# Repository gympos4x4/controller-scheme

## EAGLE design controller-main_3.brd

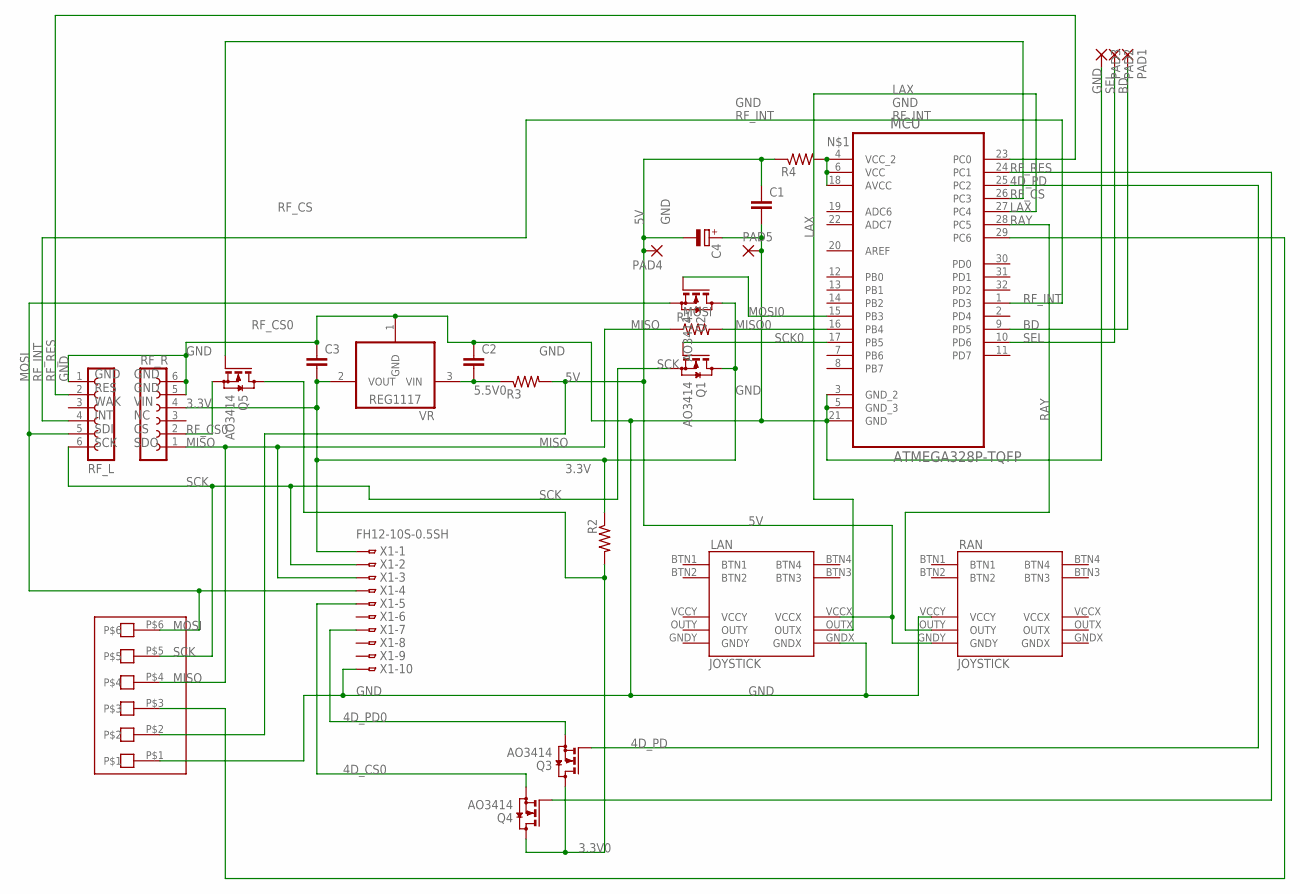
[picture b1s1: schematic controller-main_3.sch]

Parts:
C1, C2, C3: C-EUC1206; C1206
C4: CPOL-EU153CLV-0505; 153CLV-0505
LAN: JOYSTICK
MCU: ATMEGA328P-TQFP; QFP80P900X900X120-32N
PAD1, PAD2, PAD3: SMD2; SMD1,27-2,54
PAD4, PAD5: SMD5; SMD2,54-5,08
Q1, Q2, Q3, Q4, Q5: AO3414; SOT23
R1, R2, R3, R4: R-US_R1206; R1206
RAN: JOYSTICK
RF_L: FE06-1; FE06
RF_R: FE06-1; FE06
U$1: JTECH-6PV; PAK-6PV
VR: REG1117; SOT223
X1: FH12-10S-0.5SH

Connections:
3.3V: C3.2, Q1.3 (D), Q2.3 (D), R2.1, RF_R.4, VR.2 (VOUT), X1.1
3.3V0: Q3.3 (D), Q4.3 (D), Q5.3 (D), R2.2
4D_CS: MCU.24 (PC1), Q4.1 (G)
4D_CS0: Q4.2 (S), X1.5
4D_PD: MCU.25 (PC2), Q3.1 (G)
4D_PD0: Q3.2 (S), X1.7
5.5V0: C2.2, R3.1, VR.3 (VIN)
5V: C1.1, C4.-, LAN.VCCX, PAD4.1, R3.2, R4.1, RAN.GNDY, U$1.P$2
BD: MCU.9 (PD5), PAD1.1
GND: C1.2, C2.1, C3.1, C4.+, LAN.GNDX, MCU.3 (GND_2), MCU.5 (GND_3), MCU.21 (GND), PAD3.1, PAD5.1, RAN.VCCY, RF_L.1, RF_R.5, RF_R.6, U$1.P$1, VR.1 (GND), X1.10
LAX: LAN.OUTX, MCU.27 (PC4)
MISO: R1.1, RF_R.1, U$1.P$4, X1.3
MISO0: MCU.16 (PB4), R1.2
MOSI: Q2.2 (S), RF_L.5, U$1.P$6, X1.4
MOSI0: MCU.15 (PB3), Q2.1 (G)
unnamed: MCU.4 (VCC_2), MCU.6 (VCC), MCU.18 (AVCC), R4.2
RAY: MCU.28 (PC5), RAN.OUTY
RF_CS: MCU.26 (PC3), Q5.1 (G)
RF_CS0: Q5.2 (S), RF_R.2
RF_INT: MCU.1 (PD3), RF_L.4
RF_RES: MCU.23 (PC0), RF_L.2
RST: MCU.29 (PC6), U$1.P$3
SCK: Q1.2 (S), RF_L.6, U$1.P$5, X1.2
SCK0: MCU.17 (PB5), Q1.1 (G)
SEL: MCU.10 (PD6), PAD2.1

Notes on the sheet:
GND RES WAK INT SDI SCK
GND GND VIN NC CS SDO

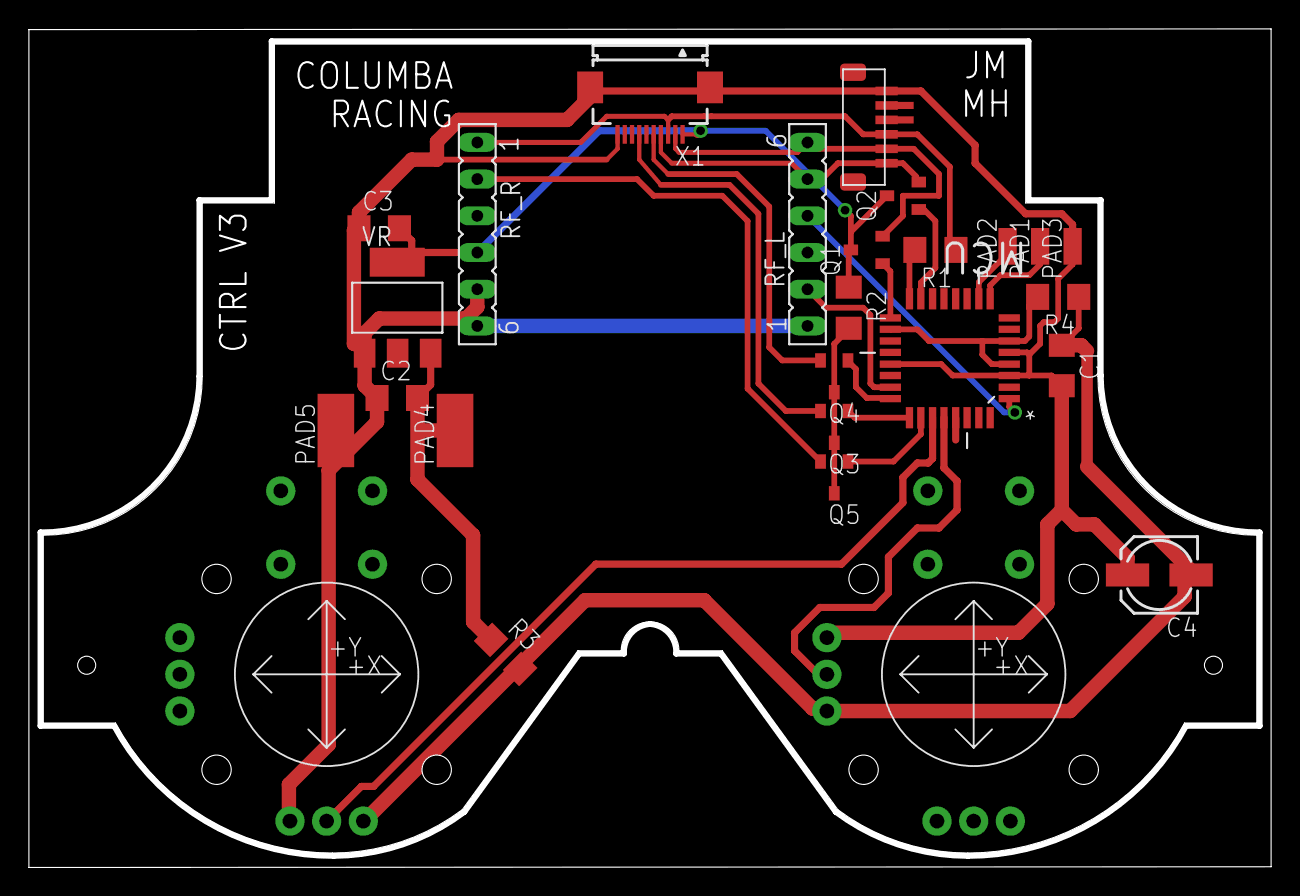
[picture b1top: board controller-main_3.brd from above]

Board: 2 copper layers, 85.6 x 57.6 mm, 26 parts (0 on the bottom side), 25 nets.

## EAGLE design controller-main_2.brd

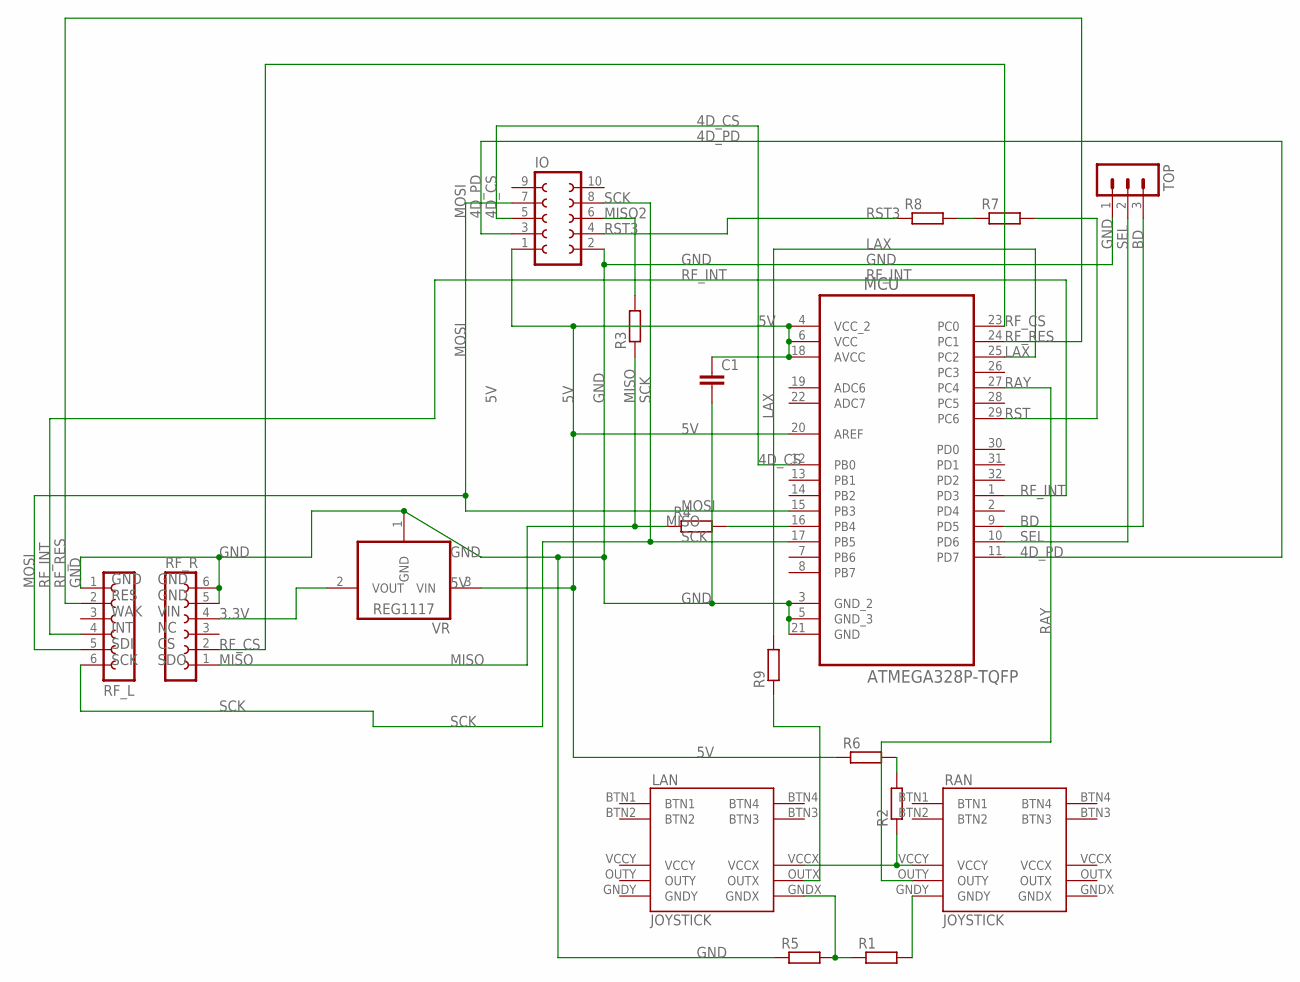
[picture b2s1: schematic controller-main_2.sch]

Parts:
C1: C-EUC1206; C1206
IO: FE05-2W
LAN: JOYSTICK
MCU: ATMEGA328P-TQFP; QFP80P900X900X120-32N
R1, R2, R3, R4, R5, R6, R7, R8, R9: R-EU_M1206; M1206
RAN: JOYSTICK
RF_L: FE06-1; FE06
RF_R: FE06-1; FE06
TOP: MA03-1
VR: REG1117; SOT223

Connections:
3.3V: RF_R.4, VR.2 (VOUT)
4D_CS: IO.5, MCU.12 (PB0)
4D_PD: IO.3, MCU.11 (PD7)
5V: C1.1, IO.1, MCU.4 (VCC_2), MCU.6 (VCC), MCU.18 (AVCC), MCU.20 (AREF), R6.1, VR.3 (VIN)
5V2: R2.2, R6.2
5V_R: LAN.VCCX, R2.1, RAN.VCCY
BD: MCU.9 (PD5), TOP.3
GND: C1.2, IO.2, MCU.3 (GND_2), MCU.5 (GND_3), MCU.21 (GND), R5.1, RF_L.1, RF_R.5, RF_R.6, TOP.1, VR.1 (GND)
GND2: LAN.GNDX, R1.1, R5.2
LAX: MCU.25 (PC2), R9.2
LAX2: LAN.OUTX, R9.1
MISO: R3.1, R4.1, RF_R.1
MISO2: IO.6, R3.2
MISO3: MCU.16 (PB4), R4.2
MOSI: IO.7, MCU.15 (PB3), RF_L.5
unnamed: R1.2, RAN.GNDY
RAY: MCU.27 (PC4), RAN.OUTY
RF_CS: MCU.23 (PC0), RF_R.2
RF_INT: MCU.1 (PD3), RF_L.4
RF_RES: MCU.24 (PC1), RF_L.2
RST: MCU.29 (PC6), R7.2
RST2: R7.1, R8.2
RST3: IO.4, R8.1
SCK: IO.8, MCU.17 (PB5), RF_L.6
SEL: MCU.10 (PD6), TOP.2

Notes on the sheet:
GND RES WAK INT SDI SCK
GND GND VIN NC CS SDO

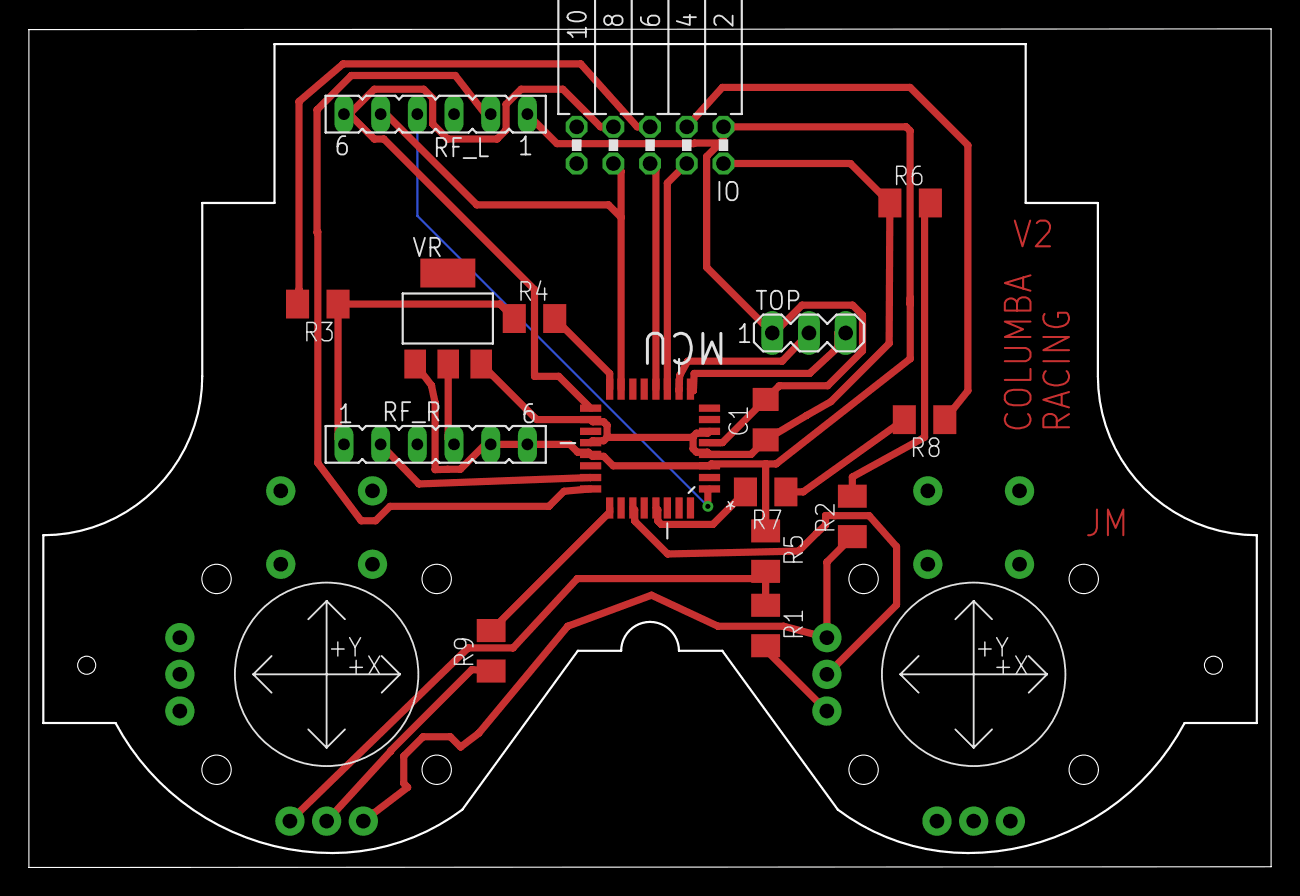
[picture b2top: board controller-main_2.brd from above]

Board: 2 copper layers, 85.8 x 57.9 mm, 18 parts (0 on the bottom side), 25 nets.

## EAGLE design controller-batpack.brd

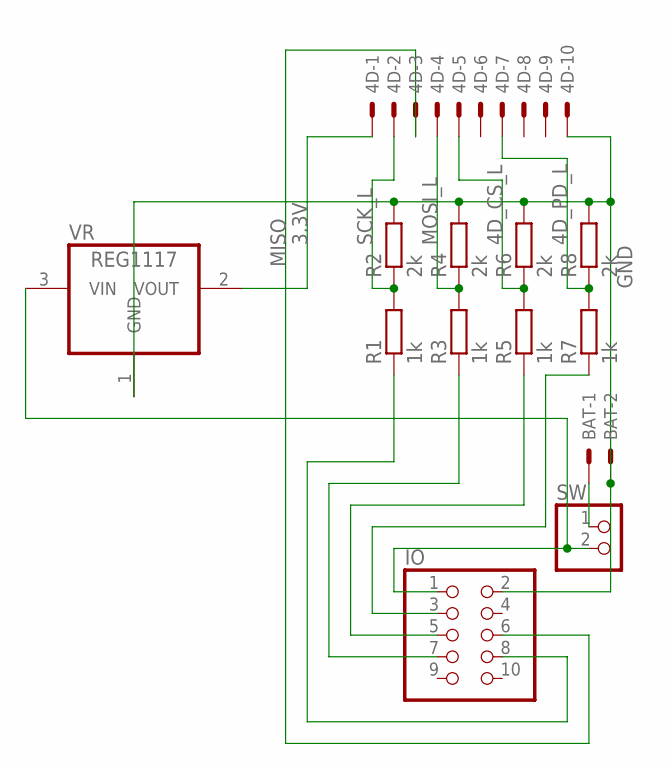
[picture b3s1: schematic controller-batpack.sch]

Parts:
4D: 52745-1090
BAT: 22-23-2021
IO: PINHD-2X5/90; 2X05/90
R1, R3, R5, R7: 1k; M1206
R2, R4, R6, R8: 2k; M1206
SW: PINHD-1X2/90; 1X02/90
VR: REG1117; SOT223

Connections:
3.3V: 4D.1, VR.2 (VOUT)
4D_CS: IO.5, R5.1
4D_CS_L: 4D.5, R5.2, R6.1
4D_PD: IO.3, R7.1
4D_PD_L: 4D.7, R7.2, R8.1
5V: IO.1, SW.2, VR.3 (VIN)
5V2: BAT.1, SW.1
GND: 4D.10, BAT.2, IO.2, R2.2, R4.2, R6.2, R8.2, VR.1 (GND)
MISO: 4D.3, IO.6
MOSI: IO.7, R3.1
MOSI_L: 4D.4, R3.2, R4.1
SCK: IO.8, R1.1
SCK_L: 4D.2, R1.2, R2.1

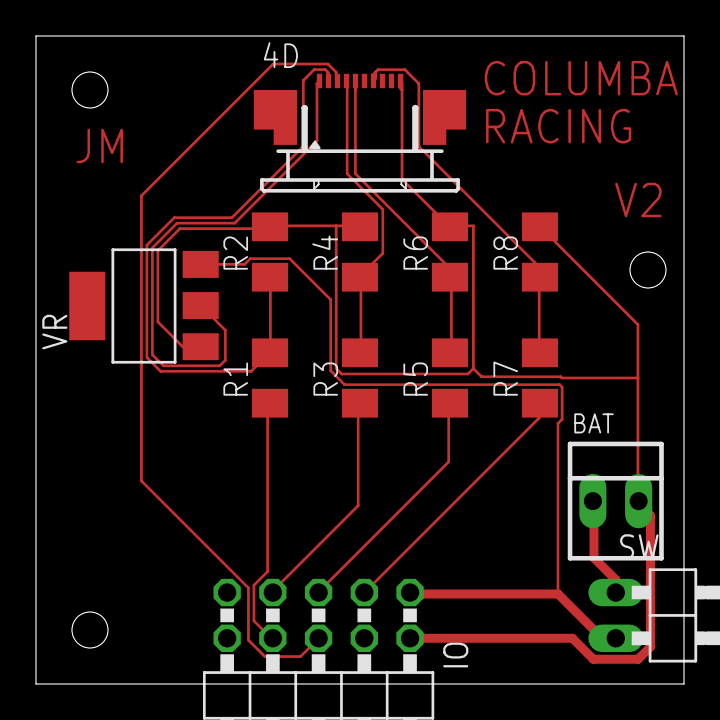
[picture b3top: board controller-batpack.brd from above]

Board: 2 copper layers, 36.0 x 36.0 mm, 13 parts (0 on the bottom side), 13 nets.

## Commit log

2017-10-17 added eagle project
2017-10-24 Updated main board
2017-10-25 updated board with display and battery
2017-10-26 added pcb design and got rid of llc in battery pack
2017-10-27 updated battery pack board
2017-11-03 finished main board
2017-11-06 Created basic main board desing
2017-11-07 Changed pin connections on the main board
2017-11-10 only half done
2017-11-10 finished the main board
2017-11-10 Created V2 main board, updated second board
2017-11-10 added project for previous commit
2017-11-11 Moved reset trace
2017-11-12 added v3
2017-11-12 Addded outline to V3 main board for milling
2017-11-24 update, I think
